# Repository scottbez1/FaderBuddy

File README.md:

# FaderBuddy

The FaderBuddy is a modular control board for 60mm motorized linear potentiometers, making it simple to add
one (or many) to a project with just 2 pins for I2C, plus power!

The control board allows you to **read** the fader position, **move** the fader to a specified position, and it can even provide **haptic feedback** and virtual detents (kind of like a linear version of my [SmartKnob](https://github.com/scottbez1/smartknob) project), all easily controlled over an I2C bus from a host controller like an ESP32.

An [ESPHome component](ABOUT_ESPHOME_INTEGRATION.md) allows
FaderBuddy assemblies to be seamlessly integrated into Home Assistant with just a few lines of yaml! 

The onboard ATtiny1616 microcontroller handles all the real-time logic (closed-loop motor control and capacitive
touch handling) and provides a simple I2C bus interface - no need to wire a motor driver/H-bridge or implement a PID control loop for each motor fader yourself.

Multiple FaderBuddy boards can be wired together and share just two I2C pins. With right-angle pin headers, you can plug adjacent FaderBuddy boards into
each other without any wires for an easy plug-and-play expandable system (supports 18mm or 19mm spacing between faders).
STEMMA QT/QWIIC-compatible connectors make it easy to hook FaderBuddy boards to the rest of your design (see [wiring diagrams](#wiring-overview) below for examples).

The [FaderBuddy community Discord server](https://discord.gg/xZXQAp5cue) is the best place to keep up with the latest changes or ask questions about the project!

<p align="center">

</p>

Learn more about the project and how to build your own below, or purchase a FaderBuddy from the [Bezek Labs Etsy store](https://bezeklabs.etsy.com/listing/4506790932/) (US-only).

---

Want to help support development or just say "thanks"? Consider a one-time or monthly sponsorship:

| [:heart: Sponsor scottbez1 on GitHub](https://github.com/sponsors/scottbez1) |
|---|

**Using this project in a commercial setting or for paid client work?** Go right ahead - it's open source (just make sure to follow the terms of the Apache License including attribution)! I would, however, ask that you consider [sponsoring the project](https://github.com/sponsors/scottbez1). Sponsorships allow me to pay for prototypes and development tools that make this project possible. Unlike pure software projects, every iteration has real hardware costs; sponsorships allow me to keep iterating and improving this and other projects faster. Thank you!

---

## ESPHome Integration

The FaderBuddy integrates seamlessly with [ESPHome](https://esphome.io/) for Home Assistant automation. The custom component provides:
- Bidirectional (input & output) position sync with Home Assistant entities
- Layer-aware automation triggers (manual_move, touch_change, double_tap)
- Per-layer haptic configuration
- Multiple faders on a single ESP32 via I2C
- 1-click firmware updates of FaderBuddy boards from Home Assistant

A simple example looks like:
```yaml
external_components:
  - source: github://scottbez1/FaderBuddy

fader_buddy:
  - id: my_fader
    on_manual_move:
      then:
        - lambda: |-
            ESP_LOGD("fader", "Fader moved to %d on layer %d", x, layer);
```

and to move the fader from a lambda:
```cpp
id(my_fader).remote_move_to(position, layer);

// optionally cap the speed - 0-255, where 255 is full speed
id(my_fader).remote_move_to(position, layer, 128);
```

That's pretty much all there is to it!

See [ABOUT_ESPHOME_INTEGRATION.md](ABOUT_ESPHOME_INTEGRATION.md) for setup instructions and many more examples.

Here's what firmware updates look like:

[Screencast from 2026-09-26 15-10-06.webm](https://github.com/user-attachments/assets/42ae8efa-67ab-416a-ac13-be791ac7859f)

## Getting Started
What you need:
- **60mm motorized fader**: Behringer MF60T faders (sold in 5-packs as replacement parts) from music/AV retailers like [Sweetwater](https://www.sweetwater.com/store/detail/MOTORFADER--behringer-mf60t-motorized-faders-set-of-5-for-motor-controllers) or [Amazon](https://www.amazon.com/Behringer-MOTOR-High-Performance-Faders-Keyboards/dp/B01DT827IC) - these appear to be manufactured by Soundwell
- **100mm motorized fader**: a separate PCB for a Soundwell 100mm fader lives at `electronics/fader_buddy_100mm`. It is not the board sold by Bezek Labs. Ordering files are in the 100mm section of [ABOUT_PCB_FABRICATION.md](ABOUT_PCB_FABRICATION.md).
- **FaderBuddy PCB**: Available [pre-assembled from Bezek Labs](https://bezeklabs.etsy.com/listing/4506790932) in the US (purchasing there directly supports this project), or use the design files fabricate and assemble your own PCBs via JLCPCB. See [ABOUT_PCB_FABRICATION.md](ABOUT_PCB_FABRICATION.md) for details.
- **ESP32**: Any ESPHome-compatible ESP32 board with 2 free GPIO pins for I2C.

> [!NOTE]
> If fabricating your own boards via JLCPCB, you'll also need to flash the firmware before use. See [ABOUT_UPDATING_FIRMWARE.md](ABOUT_UPDATING_FIRMWARE.md) for instructions.

## Wiring Overview
| Pin | Details |
| --- | --- |
| Vmot | Motor power - 5v recommended |
| Vio | Microcontroller IO power - 3.3v or 5v. This must match the voltage for the SDA/SCL I2C bus! |
| GND | Ground reference |
| SDA | I2C data. FaderBuddy includes a pull-up resistor |
| SCL | I2C clock. FaderBuddy includes a pull-up resistor |

### 3.3v MCU direct wired, direct chaining
Most common wiring for 3.3v microcontrollers like ESP32: 5 wires from host to FaderBuddy. 5v powers the motor and 3.3v powers the logic.

| HOST | FaderBuddy |
| --- | ---------- |
| 5v  | Vmot |
| 3.3v | Vio |
| GND | GND |
| SDA | SDA |
| SCL | SCL |

<br clear="right" />

### 3.3v MCU STEMMA QT
For a microcontroller with a STEMMA QT connector, the FaderBuddy requires an additional 5v wire to power the motor. Additional faders can be chained directly using the pin headers with no extra wires.

| HOST | FaderBuddy |
| --- | ---------- |
| STEMMA QT | STEMMA QT |
| 5v  | Vmot |

<br clear="right" />
<br />

Alternatively, FaderBuddy boards can be chained using STEMMA QT cables, but an additional 5v wire is also required between each board in that case.
<br clear="right" />

### 5v STEMMA QT
If you have a device that has 5v IO and a 5v STEMMA QT connector (e.g. MCP2221 with the solder jumper bridged to set 5v IO)

| HOST | FaderBuddy |
| --- | ---------- |
| STEMMA QT | STEMMA QT |

You must also bridge the V<sub>MOT</sub> ↔ V<sub>IO</sub> solder bridge on _each_ FaderBuddy so that the 5v IO can be shared with the motor driver.

_Be careful when using these solder bridges - if you leave this connection bridged and then later use the FaderBuddy in a 3.3v IO setting, the bridge will connect the 5v V<sub>MOT</sub> supply to your host 3.3v IO supply which may damage other connected devices!_

<br clear="right" />
(Board images attribution: ESP32-C3 supermini image from StudioPieters, MIT Licensed; Adafruit Qt Py and Adafruit MCP2221 images from Adafruit, Creative Commons Attribution/Share-Alike)

### Setting I2C Address
By default the FaderBuddy will use I2C address `0x20`.

When connecting more than one FaderBuddy to the same I2C bus, or if there's already another device on your bus with that address, the FaderBuddy PCB has 3 solder jumper pads allowing you to change the I2C address by bridging those pads.

| Address | A2    | A1    | A0    |
| ------- | ----- | ----- | ----- |
| `0x20`  | `[ ]` | `[ ]` | `[ ]` |
| `0x21`  | `[ ]` | `[ ]` | `[█]` |
| `0x22`  | `[ ]` | `[█]` | `[ ]` |
| `0x23`  | `[ ]` | `[█]` | `[█]` |
| `0x24`  | `[█]` | `[ ]` | `[ ]` |
| `0x25`  | `[█]` | `[ ]` | `[█]` |
| `0x26`  | `[█]` | `[█]` | `[ ]` |
| `0x27`  | `[█]` | `[█]` | `[█]` |

## Calibrating Your Fader
Once your FaderBuddy is mounted on its motorized fader and connected to Home Assistant, run a self-calibration to tune the motor control. FaderBuddy will come with a generic profile, but it may not move as smoothly or settle well.

To calibrate from Home Assistant:
1. Open the device page for your fader (**Settings → Devices & services → ESPHome**, then select your device).
2. Under **Configuration**, press **Self Calibration**.
3. Keep your hands off the fader while it sweeps the knob to both ends of its travel and back. This takes a few seconds.
4. Check the fader's **Status** sensor under **Diagnostic** - it should read `calibration succeeded`. If it reports a failure instead, it says why.

https://github.com/user-attachments/assets/dca807f0-2b44-4b6c-8e06-34a2b3fe7681

The results are stored on the FaderBuddy in flash, so you only need to do this once per board - re-run it if you move the board to a different fader or change something substantial (like adding a heavy fader cap).

## About the Board Design
The most plug-and-play option (if you're in the US) is to buy the FaderBuddy PCBs [pre-assembled from the Bezek Labs store](https://bezeklabs.etsy.com/listing/4506790932), which come with firmware already flashed, the hardware tested, and it helps support this project and future development!

To fabricate or assemble the PCBs yourself, see [ABOUT_PCB_FABRICATION.md](ABOUT_PCB_FABRICATION.md) for more info on ordering.

**Hardware details:**
- ATtiny1616 microcontroller with UPDI programming interface
- Supports 3.3v or 5v logic (with 3.3v logic, 5v is still required for powering the motor; with 5v logic Vio and Vmot can be combined for only 4 wires)
- DRV8837 motor driver, with potentiometer position feedback for closed-loop control
- JST connectors for I2C (QWIIC/STEMMA QT-compatible), or 0.1" pin headers for directly chaining adjacent boards
- Capacitive touch sensing for fader touch detection
- Power and debug status LEDs
- Compact PCB design optimized for JLCPCB assembly

<br />

A [STEP model](https://motorfader-artifacts.s3.amazonaws.com/master/electronics/fader_buddy_main.step) of the assembled board is also exported by CI, for mechanical CAD.

## Touch-compatible Fader Knobs/Caps
You don't _need_ touch capable fader caps - the FaderBuddy will work fine without them - but touch detection allows the FaderBuddy to cancel a motor movement if it detects a touch along the way, preventing the fader from "fighting" against the user. It also allows the FaderBuddy to detect if a user is touching the fader even if they aren't actively moving, and allows you to support a double-tap action on the fader if you'd like.

It's unfortunately nearly impossible to find off-the-shelf mass produced touch-capable fader knobs. Although the Soundwell/Behringer faders use a relatively standard 8mm x 1.2mm fader stem, pretty much all commercially available fader caps are non-conductive plastic and thus do not support touch detection, or are only available as expensive individual replacement parts (oftentimes in used condition).

However, I've found that you can 3D print touch-capable fader caps using conductive PLA filament. Although conductive PLA is generally very high resistance, this is actually a great property for making a touch detection surface.

If you don't want to print your own, you can purchase these 2-color single-piece conductive fader caps in the [Bezek Labs store](https://bezeklabs.etsy.com/listing/4501804398).

<a href="https://bezeklabs.etsy.com/listing/4501804398">

<br />

</a>

## Firmware, I2C interface, and Layers
The FaderBuddy firmware internally handles the closed loop motor control, presenting a [simple I2C interface](firmware/src/shared/i2c_data.h) that can be used to read the position and status of the board, command a movement to a position, and configure haptic feedback. This I2C interface is wrapped up in the ESPHome component, making it a great reference for how to interact with the protocol if you'd like to connect your FaderBuddy to something besides an ESP32 with ESPHome.

- Programmable haptic-feedback modes:
  - Smooth operation (no detents)
  - Magnetic endpoints (snap to 0% and 100%)
  - Configurable detents (1-15 positions)

Configuration of a FaderBuddy supports up to 8 virtual "layers", which allow a single fader to be used for multiple purposes (e.g. controlling lamp brightness and fan speed), with the host controller able
to send a single command to switch to a different layer. Switching layers restores the previous
fader position for that layer, and will apply that layer's haptic configuration.

See [ABOUT_LAYERS.md](ABOUT_LAYERS.md) for more about layers and the I2C protocol.

## Additional Documentation
This README covers the basics, but there are a number of additional pages with more detailed documentation:

- **[ABOUT_ESPHOME_INTEGRATION.md](ABOUT_ESPHOME_INTEGRATION.md)** - ESPHome setup and API reference
- **[ABOUT_LAYERS.md](ABOUT_LAYERS.md)** - Layer architecture and implementation details
- **[ABOUT_MF60T_LOW_PROFILE_MOD.md](ABOUT_MF60T_LOW_PROFILE_MOD.md)** - Optional instructions for modifying the MF60T faders so they can fit in smaller areas
- **[ABOUT_PCB_FABRICATION.md](ABOUT_PCB_FABRICATION.md)** - How to order and assemble your own FaderBuddy boards directly
- **[ABOUT_UPDATING_FIRMWARE.md](ABOUT_UPDATING_FIRMWARE.md)** - How to upload firmware to the FaderBuddy microcontroller using UPDI
- **[ABOUT_I2C_BOOTLOADER.md](ABOUT_I2C_BOOTLOADER.md)** - How firmware updates work over I2C (no UPDI programmer), via the custom bootloader in the ATtiny1616 boot section

### Project Structure
```
FaderBuddy/
├── electronics/         # KiCad PCB design files
├── firmware/            # ATtiny1616 firmware source (PlatformIO)
├── esphome/             # ESPHome custom component
│   ├── components/      # Component source code
│   └── examples/        # Example configurations
├── software/            # Software tools and demos
│   └── mcp2221-webhid/  # WebHID browser demo tool
├── production_tools/    # ESP32-based production test fixture
└── ci/                  # CI scripts for PCB export
```

## Production Testing

The `production_tools/programAndTest` directory contains unsupported (source-provided) code for programming and quality control of motor fader boards during production.

## License

FaderBuddy is released under the [Apache 2.0 License](LICENSE.txt).

In plain terms: you're free to use, modify, and distribute this project — including in commercial products — as long as you include the license with attribution to this project and indicate any changes you made. You don't have to share your modifications, but you can't claim the original work is yours or use the project name/branding to endorse your product.

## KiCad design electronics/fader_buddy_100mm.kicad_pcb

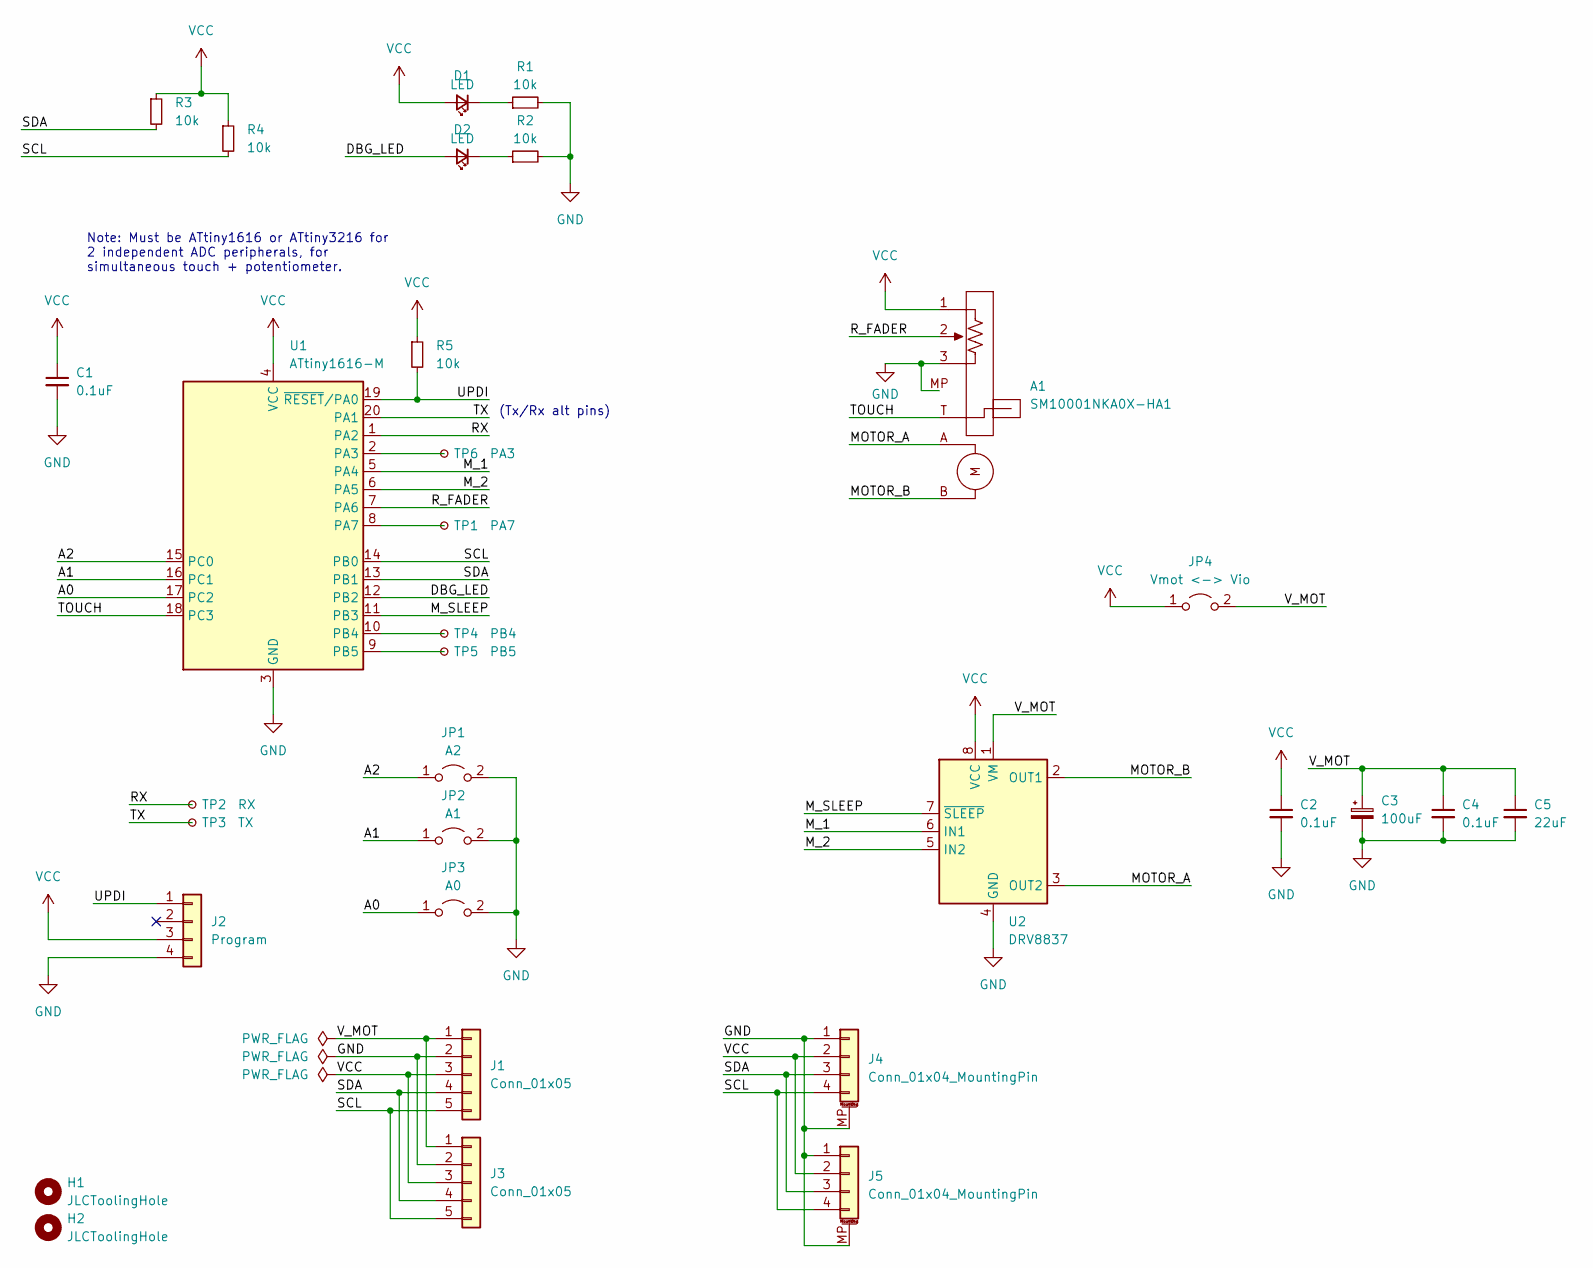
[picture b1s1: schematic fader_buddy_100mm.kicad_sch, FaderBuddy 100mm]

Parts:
A1: SM10001NKA0X-HA1
C1, C2, C4: 0.1uF; C_0603_1608Metric; LCSC C14663
C3: 100uF; CP_Elec_6.3x5.4_Nichicon; LCSC C340722
C5: 22uF; C_0805_2012Metric; LCSC C602037
D1, D2: LED; LED_0603_1608Metric; LCSC C2286
H1, H2: JLCToolingHole; AssemblyToolingHole
J1: Conn_01x05; PinSocket_1x05_P2.54mm_Horizontal_no_silk_fill
J2: Program; 1x04_P2.54mm_UPDI
J3: Conn_01x05; PinHeader_1x05_P2.54mm_Horizontal_no_pin_silk
J4, J5: Conn_01x04_MountingPin; JST_SH_SM04B-SRSS-TB_1x04-1MP_P1.00mm_Horizontal; LCSC C19270571
JP1: A2; SolderJumper-2_P1.3mm_Open_TrianglePad1.0x1.5mm_thermal_rel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
JP2: A1; SolderJumper-2_P1.3mm_Open_TrianglePad1.0x1.5mm_thermal_rel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
JP3: A0; SolderJumper-2_P1.3mm_Open_TrianglePad1.0x1.5mm_thermal_rel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
JP4: Vmot <-> Vio; SolderJumper-2_P1.3mm_Open_TrianglePad1.0x1.5mm_thermal_rel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
R1, R2, R3, R4, R5: 10k; R_0603_1608Metric; LCSC C25804
TP1: PA7; TestPoint_THTPad_D1.0mm_Drill0.5mm_small_valuesilk
TP2: RX; TestPoint_Pad_D1.5mm_ValueSilk
TP3: TX; TestPoint_Pad_D1.5mm_ValueSilk
TP4: PB4; TestPoint_THTPad_D1.0mm_Drill0.5mm_small_valuesilk
TP5: PB5; TestPoint_THTPad_D1.0mm_Drill0.5mm_small_valuesilk
TP6: PA3; TestPoint_THTPad_D1.0mm_Drill0.5mm_small_valuesilk
U1: ATtiny1616-M; VQFN-20-1EP_3x3mm_P0.4mm_EP1.7x1.7mm_with_step; LCSC C507118
U2: DRV8837; WSON-8-1EP_2x2mm_P0.5mm_EP0.9x1.6mm_solid_thermal; LCSC C191000

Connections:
/A0: JP3.1 (A), U1.17 (PC2)
/A1: JP2.1 (A), U1.16 (PC1)
/A2: JP1.1 (A), U1.15 (PC0)
/DBG_LED: D2.2 (A), U1.12 (PB2)
/MOTOR_A: A1.A, U2.3 (OUT2)
/MOTOR_B: A1.B, U2.2 (OUT1)
/M_1: U1.5 (PA4), U2.6 (IN1)
/M_2: U1.6 (PA5), U2.5 (IN2)
/M_SLEEP: U1.11 (PB3), U2.7 (~SLEEP)
/RX: TP2.1 (1_1), U1.1 (PA2)
/R_FADER: A1.2, U1.7 (PA6)
/SCL: J1.5, J3.5, J4.4, J5.4, R4.2, U1.14 (PB0)
/SDA: J1.4, J3.4, J4.3, J5.3, R3.2, U1.13 (PB1)
/TOUCH: A1.T, U1.18 (PC3)
/TX: TP3.1 (1_1), U1.20 (PA1)
/UPDI: J2.1, R5.2, U1.19 (~RESET/PA0)
/V_MOT: C3.1, C4.1, C5.1, J1.1, J3.1, JP4.2 (B), U2.1 (VM)
GND: A1.3, A1.MP, C1.2, C2.2, C3.2, C4.2, C5.2, J1.2, J2.4, J3.2, J4.1, J4.MP (MountPin), J5.1, J5.MP (MountPin), JP1.2 (B), JP2.2 (B), JP3.2 (B), R1.2, R2.2, U1.3 (GND), U1.21 (GND), U2.4 (GND), U2.9 (GND)
unnamed: D1.1 (K), R1.1
unnamed: D2.1 (K), R2.1
unnamed: TP6.1 (1_1), U1.2 (PA3)
unnamed: TP1.1 (1_1), U1.8 (PA7)
unnamed: TP4.1 (1_1), U1.10 (PB4)
unnamed: TP5.1 (1_1), U1.9 (PB5)
VCC: A1.1, C1.1, C2.1, D1.2 (A), J1.3, J2.3, J3.3, J4.2, J5.2, JP4.1 (A), R3.1, R4.1, R5.1, U1.4 (VCC), U2.8 (VCC)

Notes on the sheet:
(Tx/Rx alt pins)
Note: Must be ATtiny1616 or ATtiny3216 for 2 independent ADC peripherals, for simultaneous touch + potentiometer.

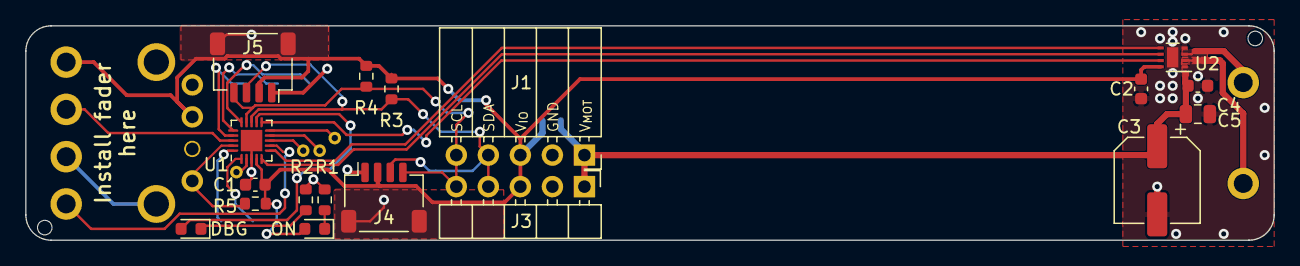
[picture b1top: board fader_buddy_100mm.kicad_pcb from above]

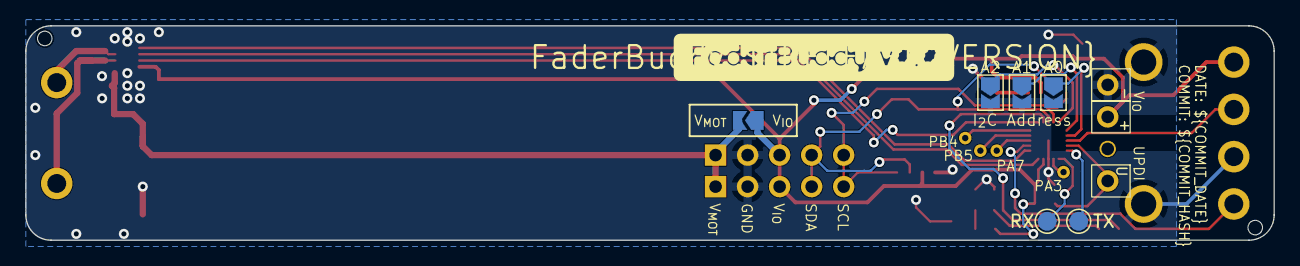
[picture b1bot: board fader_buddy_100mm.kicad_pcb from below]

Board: 2 copper layers, 99.0 x 17.0 mm, 32 parts (11 on the bottom side), 25 nets.

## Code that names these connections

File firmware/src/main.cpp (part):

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    (uint8_t)(FW_VERSION & 0xFF),
};

#define PIN_LED (PIN_PB2)
#define LED_bm (1 << 2)  // PIN_LED on VPORTB, for direct port access

// Heartbeat blink period for PIN_LED, in ms (25% duty cycle). Overridable via
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#define DEBUG_LED_BLINK_PERIOD_MS (512)
#endif

#define PIN_MOTOR_nSLEEP (PIN_PB3)
#define MOTOR_nSLEEP_bm (1 << 3)  // PIN_MOTOR_nSLEEP on VPORTB, for direct port access

// Energizing pin A moves fader toward the motor end
#define PIN_MOTOR_A (PIN_PA4)
#define PIN_MOTOR_B (PIN_PA5)

// Value increases as fader approaches the motor end
#define PIN_FADER (PIN_PA6)

#define PIN_TOUCH (PIN_PC3)

#define PIN_ADDR_0 (PIN_PC2)
#define PIN_ADDR_1 (PIN_PC1)
#define PIN_ADDR_2 (PIN_PC0)

// PWM configuration
#if defined(MILLIS_USE_TIMERA0) || defined(__AVR_ATtinyxy2__)
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
// Fixed-rate control tick, so gains and filter time constants keep the same
// meaning regardless of how long touch processing takes on a given loop().
#define CONTROL_TICK_US (500)           // 2 kHz (leaves loop headroom for touch)
#define VELOCITY_TAU_S (0.004f)         // velocity estimate smoothing, seconds

// Live gains - declared in motor_control.h, derived by motor_cal.cpp, defined
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
// Touch state
cap_sensor_t touch_sensor;
uint16_t touch_recal_count = 0;  // Count of touch recalibrations since boot

// I2C slave base address (before A0/A1/A2 jumpers are applied)
const uint8_t I2C_BASE_ADDRESS = 0x20;
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// Tap detection state
TapState tap_state = TAP_NONE;
uint32_t tap_timestamp = 0;          // Timestamp of last tap-related event for duration/timeout tracking
uint16_t tap_position_start = 0;     // Raw ADC value when first touch started
uint8_t double_tap_nonce = 0;

bool pending_report_on_idle = false;
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  
  // Configure TCA0 for single-slope PWM
  // HCMPnEN bit: port output register for the corresponding WO[n+3] pin
  // PA4=WO4=HCMP1, PA5=WO5=HCMP2
  TCA0.SPLIT.CTRLB = (TCA_SPLIT_HCMP1EN_bm | TCA_SPLIT_HCMP2EN_bm);
  TCA0.SPLIT.HPER  = 254;
  TCA0.SPLIT.HCMP1 = 0;
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}

void setup_i2c() {
  // Straight to the port. The three address jumpers are PC0-PC2, read once at
  // boot, and going through pinMode()/digitalRead() for them links both
  // functions (~120 bytes) for no benefit.
  PORTC.PIN0CTRL |= PORT_PULLUPEN_bm;
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
  // A fitted jumper pulls its pin low, so the bits are inverted. Note the
  // address pins run the opposite way round from the port bits: PIN_ADDR_0 is
  // PC2 and PIN_ADDR_2 is PC0, so the three bits are reversed, not copied.
  uint8_t fitted = (~VPORTC.IN) & 0x07;  // bit n set = jumper on PCn
  uint8_t address = I2C_BASE_ADDRESS +
    ((fitted & (1 << 0)) << 2) +  // PC0 -> A2
    ((fitted & (1 << 1))) +       // PC1 -> A1
    ((fitted & (1 << 2)) >> 2);   // PC2 -> A0

  // Initialize I2C as slave
  Wire.begin(address);
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}

void setup_touch() {
  ptc_add_selfcap_node(&touch_sensor, PIN_TO_PTC(PIN_TOUCH), 0);
  ptc_node_set_thresholds(&touch_sensor, 200, 50);
  ptc_node_set_gain(&touch_sensor, ADC_SAMPNUM_ACC1_gc, ADC_SAMPNUM_ACC1_gc);

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  setup_i2c();

  // Direct port setup, for the same reason as the address pins above.
  // PB2 LED, PB3 nSLEEP out; PA4/PA5 motor out; PA6 fader in.
  VPORTB.DIR |= LED_bm | MOTOR_nSLEEP_bm;
  VPORTA.DIR |= MOTOR_A_bm | MOTOR_B_bm;
  VPORTA.DIR &= ~(1 << 6);
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  // Using ADC1 with raw setup rather than megaTinyCore's analogRead helpers since
  // we need to leave ADC0 free for the PTC touch library.
  init_ADC1();
  ADC1.MUXPOS=0x02; //reads from PA6, ADC1 channel 2
  ADC1.CTRLB = ADC_SAMPNUM_ACC2_gc; // Accumulate 2 readings
  ADC1.CTRLA=ADC_ENABLE_bm|ADC_FREERUN_bm; //start in freerun
  ADC1.COMMAND=ADC_STCONV_bm; //start first conversion!
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  // Stop the motor so it doesn't keep driving across the reset.
  TCA0.SPLIT.HCMP1 = 0;
  TCA0.SPLIT.HCMP2 = 0;
  digitalWrite(PIN_MOTOR_A, LOW);
  digitalWrite(PIN_MOTOR_B, LOW);

  BL_ENTRY_TOKEN = BL_ENTRY_TOKEN_MAGIC;
  _PROTECTED_WRITE(RSTCTRL.SWRR, RSTCTRL_SWRE_bm);  // software reset (CCP IOREG protected)
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
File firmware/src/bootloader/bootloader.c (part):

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/* ------------------------------------------------------------------ TWI0 */

static void twi_slave_init(void) {
  /* Hardware I2C address from the three jumpers on PC0/PC1/PC2, with pull-ups.
   *
   * The address bits run the OPPOSITE way round from the port bits: the board
   * nets are PC0 = A2, PC1 = A1, PC2 = A0 (schematic pads 15/16/17), so the
   * three bits are reversed, not copied. Getting this backwards swaps the
   * addresses of every board whose A0 and A2 jumpers differ -- offsets 1<->4
   * and 3<->6 -- which makes a fader vanish from its configured address the
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  }
  uint8_t fitted = (uint8_t)(~PORTC.IN) & 0x07;  /* bit n set = jumper on PCn */
  uint8_t addr = BL_I2C_BASE_ADDRESS
    + (uint8_t)((fitted & (1 << 0)) << 2)   /* PC0 -> A2 */
    + (uint8_t)((fitted & (1 << 1)))        /* PC1 -> A1 */
    + (uint8_t)((fitted & (1 << 2)) >> 2);  /* PC2 -> A0 */

  /* TWI0 default pins are PB0 (SCL) / PB1 (SDA). tinyAVR 1-series errata: their
   * PORTB.OUT bits must be 0. External bus pull-ups are provided by the board. */
  PORTB.OUTCLR = 0x03;

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 * RTC's free-running counter rather than a hardware PWM/auto-toggle
 * peripheral -- if the main loop ever locks up, heartbeat_update() stops
 * being called and the LED visibly stops blinking instead of continuing to
 * toggle on its own. PIN_PB2, matching the application's PIN_LED
 * (firmware/src/main.cpp). */
#define LED_PORT   PORTB
#define LED_PIN_bm PIN2_bm
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/* ------------------------------------------------------ recovery strap pin */

/*
 * Forced-entry strap: TP5 (PB5), a spare pin broken out to a test point on the
 * back of the board and connected to nothing else. Ground it while the board
 * comes out of reset and the bootloader stays resident instead of starting the
 * application.
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 * app_is_valid(), but broken* -- a partially written image whose reset vector
 * happens to be programmed, or an app that boots but wedges before it serves
 * I2C. In both cases REG_ENTER_BOOTLOADER is unreachable, so without a strap the
 * only way back is UPDI. It costs nothing at normal boot: the pin is sampled
 * once and the pull-up is switched off again before the application starts.
 *
 * The strap only has to be held across reset, not for the whole update -- the
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
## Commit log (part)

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2025-01-27 Initial checkin of electronics
2025-02-02 minor updates, mostly ready
2025-02-08 A bunch of CI stuff
2025-02-08 CI updates
2025-02-08 remove old kicad plot option
2025-02-08 Update plot options
2025-02-08 CI fixes
2025-02-08 whoops
2025-02-08 Install imagemagick
2025-02-08 Remove custom font to unbreak variable replacement in exports
2025-02-08 Fix kibot release version filter
2025-02-08 Board cleanup, BOM cleanup
2025-02-24 Initial firmware
2025-02-25 Disable override/timeout
2025-05-15 WIP I2C
2025-05-15 PWM frequency
2025-05-26 Motor fader via ADC1 and working touch!
2025-05-26 Cleanup, i2c address pins
2025-05-28 i2c state data
2025-05-31 state machine
2025-05-31 better state machine
2025-06-02 working bidirectional!
2025-06-03 Updates - fix touch sticking, fix spurious input after movement, accept audible movement to avoid steady state error
2025-06-06 Haptic magnetic ends experiment
2025-08-06 Add JST SH I2C connectors
2025-08-06 Add JLC part number for I2C connectors
2025-08-06 Exclude silkscreen clipping DRC
2025-08-07 3d model and update links in readme
2025-08-07 JLC part numbers
2025-08-07 Move UPDI header
2025-08-15 OMG update the MCU part number
2025-10-20 check in
2025-10-26 Fix 32-bit state transfer, and add some test states to programAndTest
2025-10-26 Firmware upload with host script
2025-10-26 Fix self-calibration, add self-calibration to programAndTest
2025-11-06 Touch diagnostics
2025-11-06 Touch validation
2025-11-22 webhid example code
2025-11-22 basic tap detection
2025-11-23 Initial haptic config
2025-11-24 Implement detents
2025-11-24 detent strength
2025-11-25 udev rule
2026-01-03 trying to add esphome component
2026-01-03 test
2026-01-03 font issues
2026-01-03 adjust path
2026-01-04 just duplicate
2026-01-04 Adjust protocol
2026-01-04 add layer design doc
2026-01-11 layers
2026-01-11 fix esphome enum and init layer 0
2026-01-11 Plan moving layers into firmware
2026-01-11 Partial update for new layer design
2026-01-11 More layer refactors; esphome
2026-01-12 minor improvements
2026-01-12 update state before invoking triggers
2026-01-12 debugging state issues and double tap issues
2026-01-12 fix state bit bug, clean up layer changes
2026-01-12 Clean up trigger rate limiting in esphome
2026-01-16 Fix layer change issues
2026-01-16 docs updates
2026-01-20 More docs
2026-01-22 Updates, rename esphome component
2026-01-22 Move mcp2221 demo to its own directory
2026-02-05 Add getting-started documentation scaffolding for newcomers
    - Add "What You'll Need" shopping list section with TODO placeholders
    - Add "Firmware Flashing" section with UPDI Friend recommendation and PlatformIO steps
    - Add wiring diagram placeholder in intro
    - Fix broken LAYERS_DESIGN.md link in ABOUT_ESPHOME_INTEGRATION.md (now points to ABOUT_LAYERS.md)
    https://claude.ai/code/session_01Jaa7LDh4pePkeqSCe1jeaK
2026-02-05 Add fader sourcing details and assembly instructions
    - Specify Behringer MF60T as the retail fader with links to Sweetwater,
    B&H, and Amazon
    - Add assembly section explaining the 6 through-hole solder joints needed
    to attach the PCB to the fader (no SMD work required)
    - Remove connectors/headers TODO since JLCPCB assembles everything
    https://claude.ai/code/session_01Jaa7LDh4pePkeqSCe1jeaK
2026-02-06 Fill in UPDI connection details and power supply info
    - Document UPDI Friend wiring: black→(-), red→(+), white→(U) test points
    on PCB back, 0.1" spacing compatible with pin headers
    - Clarify that USB power from ESP32 is sufficient for multiple faders,
    no external supply needed
    - Note that power is carried through daisy-chain headers
    - Replace vague TODOs with specific info, keep photo and max-current TODOs
2026-02-06 Clarify any ESPHome-compatible ESP32 board will work
    https://claude.ai/code/session_01Jaa7LDh4pePkeqSCe1jeaK
2026-02-06 clean up
2026-03-06 Add demo gif to README
    Added a demo image for the motorFader project.
2026-03-22 Enhance README with images and wiring details
    Updated README.md to include images and detailed wiring instructions for motor fader setup.
2026-05-13 Add getting-started documentation scaffolding for newcomers (#2)
2026-05-13 add apache notices
2026-05-13 Document low-profile MF60T mod
2026-05-13 Add UPDI connection diagram
    Updated wiring diagram and added image link for UPDI Friend.
2026-05-13 doc updates; export rasterized schematic
2026-05-13 More doc updates
2026-05-13 Simplify README Getting Started and Wiring sections
    Replace bulky What You'll Need tables with a concise Getting Started bullet
    list, referencing ABOUT_PCB_FABRICATION.md and ABOUT_UPDATING_FIRMWARE.md for
    details. Combine the two STEMMA QT wiring subsections into one, showing direct
    pin-header chaining first then STEMMA QT chaining as an alternative.
    https://claude.ai/code/session_015KMr3dbKgFyYPshym8xkm3
2026-05-13 Simplify README Getting Started and Wiring sections (#3)
    Replace bulky What You'll Need tables with a concise Getting Started bullet
    list, referencing ABOUT_PCB_FABRICATION.md and ABOUT_UPDATING_FIRMWARE.md for
    details. Combine the two STEMMA QT wiring subsections into one, showing direct
    pin-header chaining first then STEMMA QT chaining as an alternative.
2026-05-14 revert unintentional change to electronics/motor_fader_main.kicad_pro
2026-05-14 Rename to FaderBuddy part 1 - docs
2026-05-14 Rename to FaderBuddy part 2 - esphome
2026-05-14 Rename to FaderBuddy part 3 - other firmware and software
2026-05-14 Rename to FaderBuddy part 4 - electronics updates and other ref updates
2026-05-14 Rename to FaderBuddy part 5 - misc cleanup
2026-05-15 Update README with fader cap images
    Added images and a link for conductive fader caps in the README.
2026-05-17 doc updates
2026-05-19 Improved docs
2026-05-19 try updating to kicad 10
2026-05-19 update again
2026-05-19 dont' update version
2026-05-19 drc 2
2026-05-19 schematic title block
2026-05-19 Update electronics to kicad 10 (#4)
2026-06-01 Updates from dev branch
2026-06-01 Document on_raw_position_update
2026-06-07 README updates
2026-06-08 More readme updates
2026-06-08 a few small doc tweaks
2026-06-23 Update gif in readme

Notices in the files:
firmware/src/bootloader/bootloader.c:
Copyright 2026 Scott Bezek
Licensed under the Apache License, Version 2.0 (the "License");
